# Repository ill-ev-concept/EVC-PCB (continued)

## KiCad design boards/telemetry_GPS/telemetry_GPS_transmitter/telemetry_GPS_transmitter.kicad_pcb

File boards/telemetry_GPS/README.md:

## Cart Orders

Mouser Cart(enough for 1 board, with some +/- tolerance in the number of parts): [https://www.mouser.com/en/Tools/SavedCart/Share?AccessID=581db3815b](https://www.mouser.com/en/Tools/SavedCart/Share?AccessID=141096782c)

Digikey Cart(enough for 2 transmitters, 2 receivers): [https://www.digikey.com/short/j81pmn1m](https://www.digikey.com/short/2zj99zv8)](https://www.digikey.com/short/7t22bw8j)](https://www.digikey.com/short/md8pf59v)

E-Shop Order (these need to be added to the carts):

## Block Diagram

## Common Issues/Tips

- The recommended way to solder this board is to use a stencil for the top side, place all components (except for buttons & connectors) on the solder paste, and use a reflow oven. For the back side, it's recommended to use the backside stencil as well as a heat gun. Try to be careful with applying heat around the UBLOX NEO-M8N area. DO NOT UNDER ANY CIRCUMSTANCES SOLDER THE BACK SIDE IN AN OVEN AFTER REFLOWING THE TOP SIDE.
- Always use a microscope when debugging your soldering of the telemetry "Scout" board
- Stencil
  - Make sure that the stencil is relatively flat onto the board, otherwise you'll do multiple tries and end up with way too much paste
  - Pins shouldn't have a ton of solder but always make sure to check that EVERY pin has solder
- MCU Orientation
  - The dot on the bottom left of the MCU marks pin 1, don't be fooled by anything else. If you did it correctly, the ST logo should be on the bottom left while looking at the board top-down, and the U1 label on the left side of the MCU
- BGA
  - The BALFHB uses BGA pins. These pins already come pre-tinned so do not apply solder on those pads, simply place the component down onto the pads.
  - If you suspect that the component is not flush/a couple pins are unconnected, apply flux and use the heat gun, flux is your best friend

## Instructions for a future V2 board
- Look into storing the data onto an SD card
- Add an LED to the GPS chip's PPS to verify that it is on
- Add more test points in general
- Do research into expanding the BALFHB into actual inductors and capacitors to make soldering the board less annoying

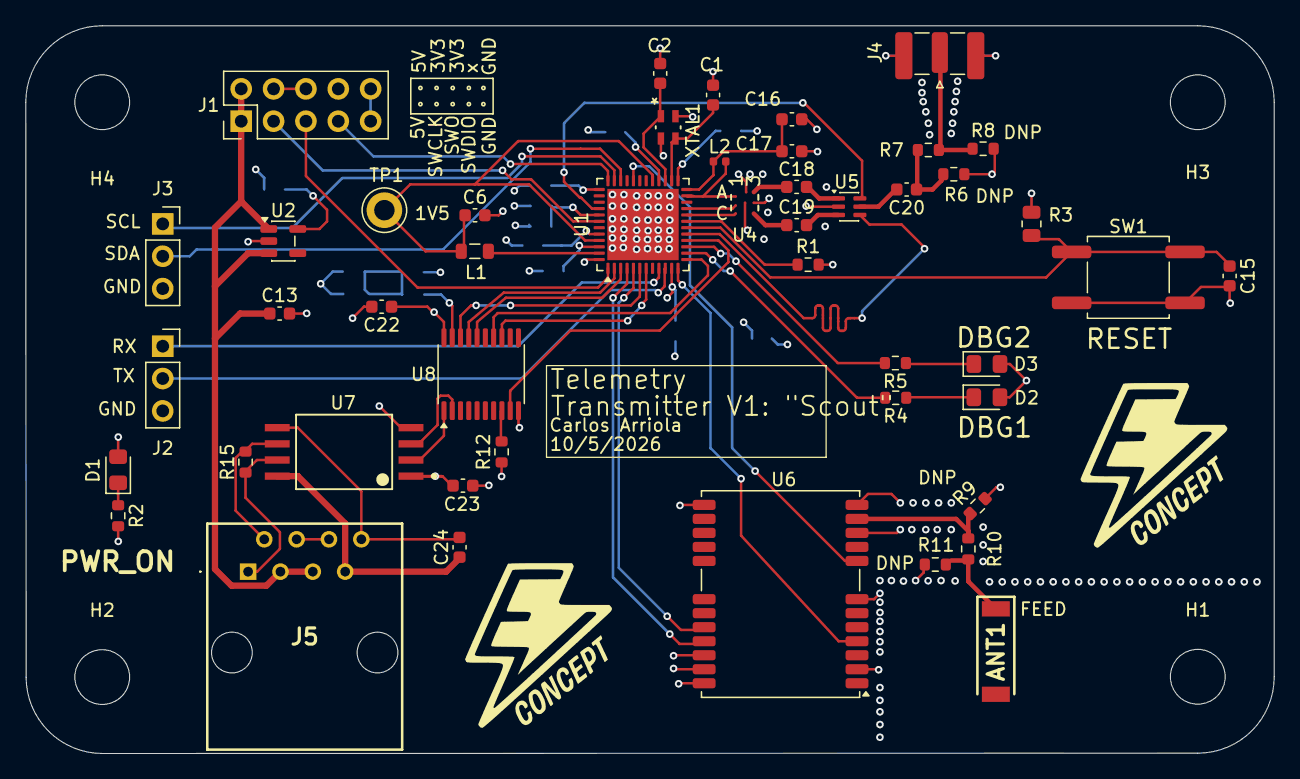
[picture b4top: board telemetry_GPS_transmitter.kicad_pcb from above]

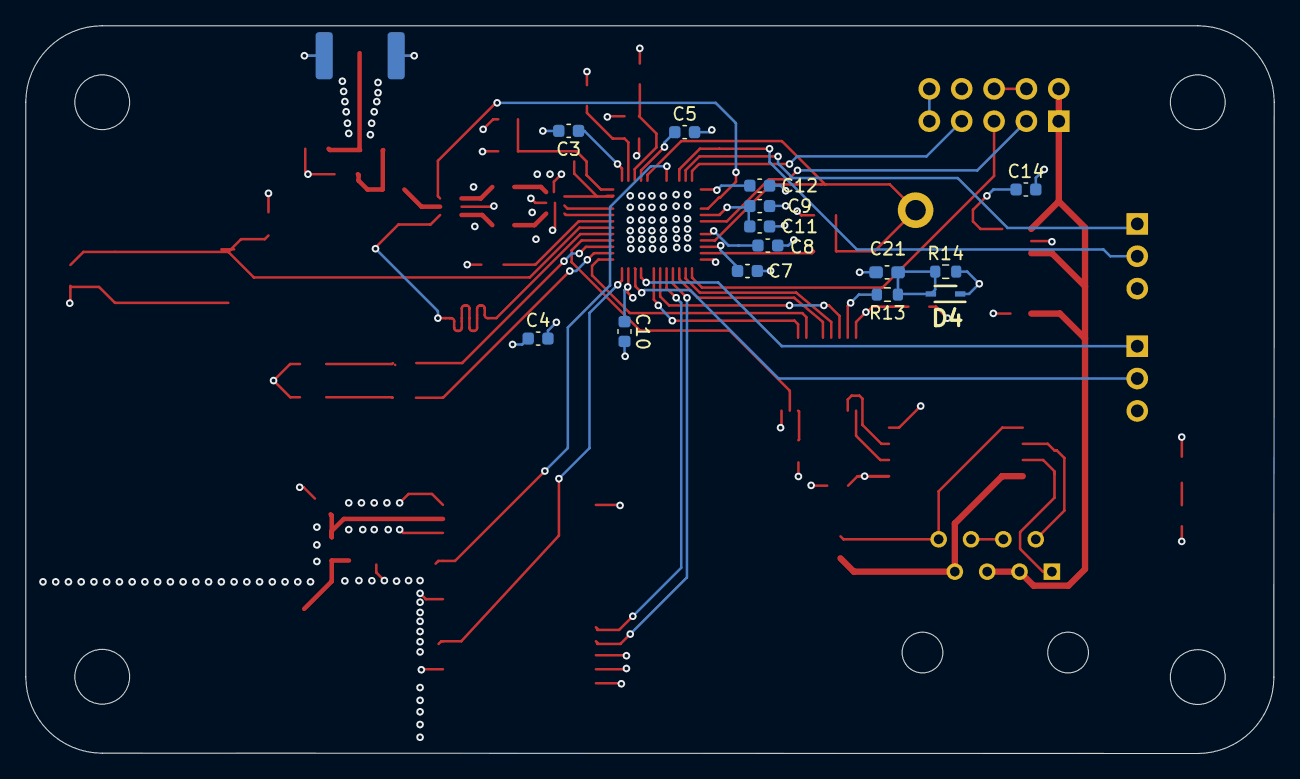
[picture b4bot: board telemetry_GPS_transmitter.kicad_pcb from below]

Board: 4 copper layers, 98.0 x 57.1 mm, 67 parts (14 on the bottom side), 55 nets.

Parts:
ANT1: 1575AT43A0040001E; ANTC7020X90N
C1, C2: 6pF; C_0603_1608Metric
C3, C5, C7, C8, C10, C15, C22, C23, C24: 0.1uF; C_0603_1608Metric
C4, C11, C12: 4.7uF; C_0603_1608Metric
C6: 470nF; C_0603_1608Metric
C9: 0.01uF; C_0603_1608Metric
C13, C14: 1uF; C_0603_1608Metric
C16: 47nF; C_0603_1608Metric
C17: 68pF; C_0603_1608Metric
C18, C19, C20: 1000pF; C_0603_1608Metric
C21: 2.2nF; C_0603_1608Metric_Pad1.08x0.95mm_HandSolder
D1, D2, D3: LED_Green; LED_0805_2012Metric_Pad1.15x1.40mm_HandSolder
D4: 1N4148WS; SODFL2512X90N
G1, G1#2: LOGO; EVC_LOGO
H1, H2, H3, H4: MountingHole; MountingHole_4.3mm_M4
J1: Conn_02x05_Odd_Even; PinHeader_2x05_P2.54mm_Vertical
J2, J3: Conn_01x03; PinSocket_1x03_P2.54mm_Vertical
J4: Conn_Coaxial; SMA_Samtec_SMA-J-P-H-ST-EM1_EdgeMount
J5: 54602-908LF; 54602908LF
L1: 15uH; L_0805_2012Metric
L2: 47nH (High Q); L_0402_1005Metric
R1: 10K; R_0603_1608Metric
R2, R4, R5: 330R; R_0603_1608Metric
R3: 100k; R_0805_2012Metric
R6, R8, R9, R11: R; R_0603_1608Metric
R7, R10: 0R; R_0603_1608Metric
R12, R13: 10k; R_0603_1608Metric
R14: 1k; R_0603_1608Metric
R15: 120R; R_0603_1608Metric
SW1: SW_Push; SW_Push_1P1T_NO_CK_KSC9xxG
TP1: TestPoint; TestPoint_Keystone_5010-5014_Multipurpose
U1: STM32WL55CCUx; QFN-48-1EP_7x7mm_P0.5mm_EP5.6x5.6mm
U2: TLV75509PDBV; SOT-23-5
U4: BALFHB-WL-02D3; CSPG8_STM
U5: MASW-007221; SOT-363_SC-70-6
U6: NEO-M8N; ublox_NEO
U7: ISO1042QDWVQ1; DWV0008A-IPC_B
U8: MCP2515-xST; TSSOP-20_4.4x6.5mm_P0.65mm
XTAL1: NX2016SA-32MHZ-EXS00A-CS07977; NX2016SA_NDK

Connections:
+1V5: C6.1, L1.1, TP1.1 (1_1), U1.29 (VDDRF1V55), U1.45 (VFBSMPS)
+3V3: C3.1, C4.1, C5.1, C7.1, C8.1, C9.1, C10.1, C11.1, C12.1, C14.1, C22.1, C23.1, D1.2 (A), D2.2 (A), D3.2 (A), D4.1 (K), J1.4, J1.6, R3.1, R14.2, U1.11 (VDD), U1.25 (VDDPA), U1.28 (VDDRF), U1.37 (VBAT), U1.41 (VDDA), U1.44 (VDD), U1.46 (VDDSMPS), U2.5 (OUT), U6.2 (D_SEL), U6.22 (V_BCKP), U6.23 (VCC), U7.1 (VCC1), U8.20 (VDD)
+5V: C13.1, J1.1, J1.2, J5.3, J5.5, U2.1 (IN), U2.3 (EN)
/CAN/5VCAN: C24.1, J5.7, U7.8 (VCC2)
/CAN/CANH: J5.1, R15.1, U7.7 (CANH)
/CAN/CANL: J5.2, R15.2, U7.6 (CANL)
/CAN/CAN_RX: U7.3 (RXD), U8.2 (RXCAN)
/CAN/CAN_TX: U7.2 (TXD), U8.1 (TXCAN)
/CAN/CS_N: U1.6 (PB8), U8.18 (~CS)
/CAN/EXT_CLK: U1.16 (PA8), U8.9 (OSC1)
/CAN/GNDCAN: C24.2, J5.8, U7.5 (GND2)
/CAN/INT_N: U1.7 (PA0), U8.13 (~INT)
/CAN/SCLK: U1.13 (PA5), U8.14 (SCK)
/CAN/SLAVE_I: U1.3 (PB5), U8.16 (SI)
/CAN/SLAVE_O: U1.2 (PB4), U8.17 (SO)
/Debug/DBG_LED_1: R4.2, U1.14 (PA6)
/Debug/DBG_LED_2: R5.2, U1.15 (PA7)
/Debug/I2C_SCL: J3.1, U1.35 (PA12)
/Debug/I2C_SDA: J3.2, U1.34 (PA11)
/Debug/MCU_UART_RX: J2.2, U1.10 (PA3)
/Debug/MCU_UART_TX: J2.1, U1.9 (PA2)
/Debug/NRST: C15.1, R3.2, SW1.1, U1.18 (NRST)
/Debug/SWCLK: J1.3, U1.42 (PA14)
/Debug/SWDIO: J1.7, U1.36 (PA13)
/Debug/SWO: J1.5, U1.1 (PB3)
/GPS/RESET_N: U1.32 (PB12), U6.8 (~RESET)
/GPS/RTC_IN: U1.12 (PA4), U6.4 (EXTINT)
/GPS/RXD: U1.4 (PB6), U6.21 (RXD/SPI_MOSI)
/GPS/TXD: U1.5 (PB7), U6.20 (TXD/SPI_MISO)
/RF/RFI_N: U1.21 (RFI_N), U4.A2 (RFI_N_OUT)
/RF/RFI_P: U1.20 (RFI_P), U4.A3 (RFI_P_OUT)
/RF/RFO_HP: L2.2, U1.23 (RFO_HP), U4.A1 (RFO_IN)
/RF/RF_I: C19.1, U4.C3 (RFI_IN)
/RF/RF_O: C18.2, U4.C1 (RFO_OUT)
/RF/RF_TX_EN: U1.40 (PC15), U5.6 (V1)
/RF/RF_TX_EN_N: U1.17 (PA9), U5.4 (V2)
/RF/VR_PA: C16.1, C17.1, L2.1, U1.24 (VR_PA)
/STM32/OSC_IN: C1.1, U1.26 (OSC_IN), XTAL1.1
/STM32/OSC_OUT: C2.1, U1.27 (OSC_OUT), XTAL1.3
GND: C1.2, C2.2, C3.2, C4.2, C5.2, C6.2, C7.2, C8.2, C9.2, C10.2, C11.2, C12.2, C13.2, C14.2, C15.2, C16.2, C17.2, C21.2, C22.2, C23.2, J1.9, J1.10, J2.3, J3.3, J4.2 (Ext), J5.4, J5.6, R1.2, R2.2, R6.2, R8.2, R9.2, R11.2, R12.1, SW1.2, U1.48 (VSSSMPS), U1.49 (VSS), U2.2 (GND), U4.B1 (GND2), U4.B2 (GND3), U4.C2 (GND1), U5.2 (GND), U6.7 (VDD_USB), U6.10 (GND), U6.12 (GND), U6.13 (GND), U6.24 (GND), U7.4 (GND1), U8.10 (VSS), XTAL1.2, XTAL1.4
unnamed: ANT1.1 (FEED_1), R10.2, R11.1
unnamed: C20.1, R6.1, R7.1
unnamed: D1.1 (K), R2.1
unnamed: D2.1 (K), R4.1
unnamed: D3.1 (K), R5.1
unnamed: C21.1, D4.2 (A), R13.1, R14.1
unnamed: J4.1 (In), R7.2, R8.1
unnamed: R1.1, U1.19 (PH3)
unnamed: L1.2, U1.47 (VLXSMPS)
unnamed: C18.1, U5.1 (RF1)
unnamed: C19.2, U5.3 (RF2)
unnamed: C20.2, U5.5 (RFC)
unnamed: R9.1, R10.1, U6.11 (RF_IN)
unnamed: R12.2, U8.8 (OSC2)
unnamed: R13.2, U8.19 (~RESET)

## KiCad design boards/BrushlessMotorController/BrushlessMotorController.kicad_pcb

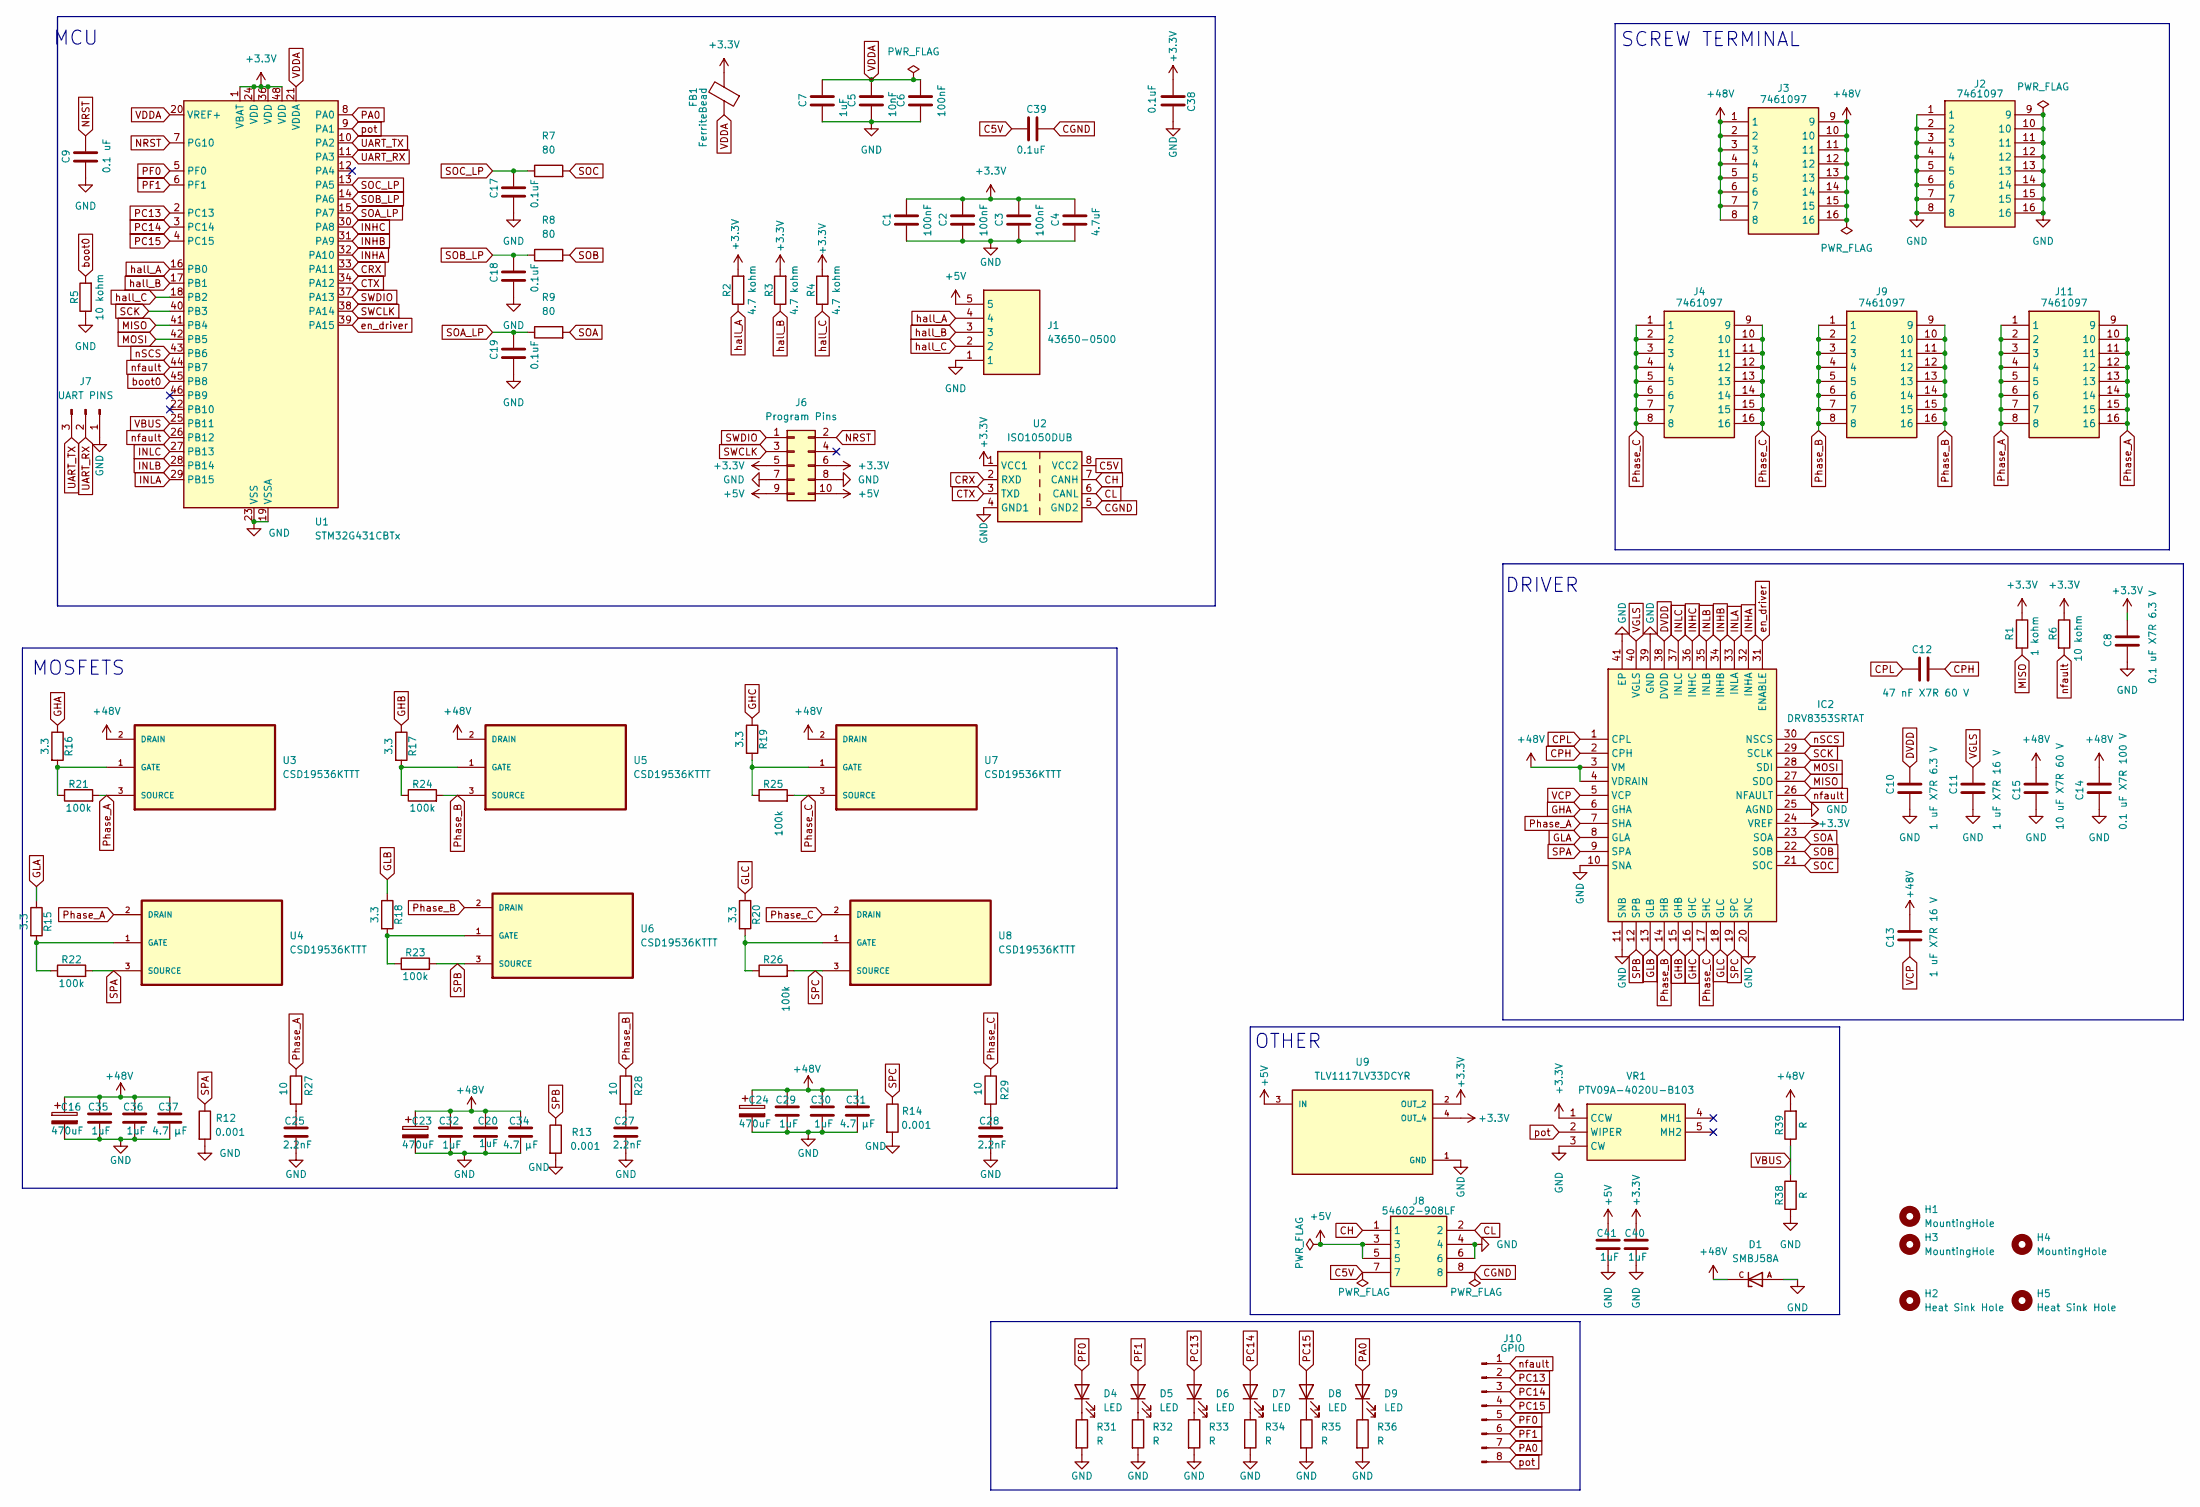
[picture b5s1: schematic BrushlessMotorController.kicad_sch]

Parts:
C1, C2, C3, C6: 100nF; C_0805_2012Metric_Pad1.18x1.45mm_HandSolder
C4: 4.7uF; C_0805_2012Metric_Pad1.18x1.45mm_HandSolder
C5: 10nF; C_0805_2012Metric_Pad1.18x1.45mm_HandSolder
C7, C40, C41: 1uF; C_0805_2012Metric_Pad1.18x1.45mm_HandSolder
C8: 0.1 uF X7R 6.3 V; C_0805_2012Metric_Pad1.18x1.45mm_HandSolder
C9: 0.1 uF; C_0805_2012Metric_Pad1.18x1.45mm_HandSolder
C10: 1 uF X7R 6.3 V; C_0805_2012Metric_Pad1.18x1.45mm_HandSolder
C11, C13: 1 uF X7R 16 V; C_0805_2012Metric_Pad1.18x1.45mm_HandSolder
C12: 47 nF X7R 60 V; C_0805_2012Metric_Pad1.18x1.45mm_HandSolder
C14: 0.1 uF X7R 100 V; C_0805_2012Metric_Pad1.18x1.45mm_HandSolder
C15: 10 uF X7R 60 V; C_1210_3225Metric_Pad1.33x2.70mm_HandSolder
C16, C23, C24: 470uF; CP_Radial_D16.0mm_P7.50mm
C17, C18, C19: 0.1uF; C_0603_1608Metric_Pad1.08x0.95mm_HandSolder
C20, C29, C30, C32, C35, C36: 1uF; C_1210_3225Metric
C25, C27, C28: 2.2nF; C_1210_3225Metric
C31, C34, C37: 4.7 µF; C_1210_3225Metric
C38, C39: 0.1uF; C_0805_2012Metric_Pad1.18x1.45mm_HandSolder
D1: SMBJ58A; DIOM4336X265N; PARTREV F2102
D4, D5, D6, D7, D8, D9: LED; LED_0603_1608Metric_Pad1.05x0.95mm_HandSolder
FB1: FerriteBead; R_0805_2012Metric_Pad1.20x1.40mm_HandSolder
H1, H3, H4: MountingHole; MountingHole_3.2mm_M3
H2, H5: Heat Sink Hole; MountingHole_3.2mm_M3
IC2: DRV8353SRTAT; QFN50P600X600X80-41N; Mouser Part Number 595-DRV8353SRTAT
J1: 43650-0500; 43650-05_00,01,02_; Mouser Part Number 538-43650-0500
J2, J3, J4, J9, J11: 7461097; Mouser Part Number 710-7461097
J6: Program Pins; PinHeader_2x05_P2.54mm_Vertical
J7: UART PINS; PinHeader_1x03_P2.54mm_Vertical
J8: 54602-908LF; 54602908LF; Manufacturer_Part_Number 54602-908LF
J10: GPIO; PinHeader_1x08_P2.54mm_Vertical
R1: 1 kohm; R_0805_2012Metric_Pad1.20x1.40mm_HandSolder
R2, R3, R4: 4.7 kohm; R_0805_2012Metric_Pad1.20x1.40mm_HandSolder
R5, R6: 10 kohm; R_0805_2012Metric_Pad1.20x1.40mm_HandSolder
R7, R8, R9: 80; R_0603_1608Metric
R12, R13, R14: 0.001; R_2512_6332Metric_Pad1.40x3.35mm_HandSolder
R15, R16, R17, R18, R19, R20: 3.3; R_0805_2012Metric_Pad1.20x1.40mm_HandSolder
R21, R22, R23, R24, R25, R26: 100k; R_0805_2012Metric_Pad1.20x1.40mm_HandSolder
R27, R28, R29: 10; R_0805_2012Metric_Pad1.20x1.40mm_HandSolder
R31, R32, R33, R34, R35, R36, R38, R39: R; R_0805_2012Metric_Pad1.20x1.40mm_HandSolder
U1: STM32G431CBTx; LQFP-48_7x7mm_P0.5mm
U2: ISO1050DUB; SOP-8_6.62x9.15mm_P2.54mm
U3, U4, U5, U6, U7, U8: CSD19536KTTT; TO254P1524X483-4N
U9: TLV1117LV33DCYR; VREG_TLV1117LV33DCYR; PARTREV B
VR1: PTV09A-4020U-B103; PTV09A4020UB103; Mouser Part Number 652-PTV09A-4020UB103

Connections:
+3.3V: C1.1, C2.1, C3.1, C4.1, C8.1, C38.2, C40.2, FB1.2, IC2.24 (VREF), J6.5, J6.6, R1.1, R2.2, R3.2, R4.2, R6.1, U1.1 (VBAT), U1.24 (VDD), U1.36 (VDD), U1.48 (VDD), U2.1 (VCC1), U9.2 (OUT_2), U9.4 (OUT_4), VR1.1 (CCW)
+5V: C41.2, J1.5, J6.9, J6.10, J8.3, J8.5, U9.3 (IN)
+48V: C13.1, C14.1, C15.1, C16.1, C20.1, C23.1, C24.1, C29.2, C30.2, C31.2, C32.2, C34.2, C35.2, C36.2, C37.2, D1.C, IC2.3 (VM), IC2.4 (VDRAIN), J3.1, J3.2, J3.3, J3.4, J3.5, J3.6, J3.7, J3.8, J3.9, J3.10, J3.11, J3.12, J3.13, J3.14, J3.15, J3.16, R39.2, U3.2 (DRAIN), U5.2 (DRAIN), U7.2 (DRAIN)
C5V: C39.2, J8.7, U2.8 (VCC2)
CGND: C39.1, J8.8, U2.5 (GND2)
CH: J8.1, U2.7 (CANH)
CL: J8.2, U2.6 (CANL)
CPH: C12.1, IC2.2 (CPH)
CPL: C12.2, IC2.1 (CPL)
CRX: U1.33 (PA11), U2.2 (RXD)
CTX: U1.34 (PA12), U2.3 (TXD)
DVDD: C10.1, IC2.38 (DVDD)
GHA: IC2.6 (GHA), R16.1
GHB: IC2.15 (GHB), R17.1
GHC: IC2.16 (GHC), R19.1
GLA: IC2.8 (GLA), R15.1
GLB: IC2.13 (GLB), R18.1
GLC: IC2.18 (GLC), R20.1
GND: C1.2, C2.2, C3.2, C4.2, C5.2, C6.2, C7.2, C8.2, C9.2, C10.2, C11.2, C14.2, C15.2, C16.2, C17.2, C18.2, C19.2, C20.2, C23.2, C24.2, C25.1, C27.1, C28.1, C29.1, C30.1, C31.1, C32.1, C34.1, C35.1, C36.1, C37.1, C38.1, C40.1, C41.1, D1.A, IC2.10 (SNA), IC2.11 (SNB), IC2.20 (SNC), IC2.25 (AGND), IC2.39 (GND), IC2.41 (EP), J1.1, J2.1, J2.2, J2.3, J2.4, J2.5, J2.6, J2.7, J2.8, J2.9, J2.10, J2.11, J2.12, J2.13, J2.14, J2.15, J2.16, J6.7, J6.8, J7.1, J8.4, J8.6, R5.1, R12.2, R13.2, R14.2, R31.2, R32.2, R33.2, R34.2, R35.2, R36.2, R38.1, U1.19 (VSSA), U1.23 (VSS), U1.35 (VSS), U1.47 (VSS), U2.4 (GND1), U9.1 (GND), VR1.3 (CW)
INHA: IC2.32 (INHA), U1.32 (PA10)
INHB: IC2.34 (INHB), U1.31 (PA9)
INHC: IC2.36 (INHC), U1.30 (PA8)
INLA: IC2.33 (INLA), U1.29 (PB15)
INLB: IC2.35 (INLB), U1.28 (PB14)
INLC: IC2.37 (INLC), U1.27 (PB13)
MISO: IC2.27 (SDO), R1.2, U1.41 (PB4)
MOSI: IC2.28 (SDI), U1.42 (PB5)
NRST: C9.1, J6.2, U1.7 (PG10)
unnamed: C25.2, R27.2
unnamed: C27.2, R28.2
unnamed: C28.2, R29.2
unnamed: D4.1 (K), R31.1
unnamed: D5.1 (K), R32.1
unnamed: D6.1 (K), R33.1
unnamed: D7.1 (K), R34.1
unnamed: D8.1 (K), R35.1
unnamed: D9.1 (K), R36.1
unnamed: R16.2, R21.1, U3.1 (GATE)
unnamed: R15.2, R22.1, U4.1 (GATE)
unnamed: R17.2, R24.1, U5.1 (GATE)
unnamed: R18.2, R23.1, U6.1 (GATE)
unnamed: R19.2, R25.1, U7.1 (GATE)
unnamed: R20.2, R26.1, U8.1 (GATE)
PA0: D9.2 (A), J10.7, U1.8 (PA0)
PC13: D6.2 (A), J10.2, U1.2 (PC13)
PC14: D7.2 (A), J10.3, U1.3 (PC14)
PC15: D8.2 (A), J10.4, U1.4 (PC15)
PF0: D4.2 (A), J10.5, U1.5 (PF0)
PF1: D5.2 (A), J10.6, U1.6 (PF1)
Phase_A: IC2.7 (SHA), J11.1, J11.2, J11.3, J11.4, J11.5, J11.6, J11.7, J11.8, J11.9, J11.10, J11.11, J11.12, J11.13, J11.14, J11.15, J11.16, R21.2, R27.1, U3.3 (SOURCE), U4.2 (DRAIN)
Phase_B: IC2.14 (SHB), J9.1, J9.2, J9.3, J9.4, J9.5, J9.6, J9.7, J9.8, J9.9, J9.10, J9.11, J9.12, J9.13, J9.14, J9.15, J9.16, R24.2, R28.1, U5.3 (SOURCE), U6.2 (DRAIN)
Phase_C: IC2.17 (SHC), J4.1, J4.2, J4.3, J4.4, J4.5, J4.6, J4.7, J4.8, J4.9, J4.10, J4.11, J4.12, J4.13, J4.14, J4.15, J4.16, R25.2, R29.1, U7.3 (SOURCE), U8.2 (DRAIN)
SCK: IC2.29 (SCLK), U1.40 (PB3)
SOA: IC2.23 (SOA), R9.2
SOA_LP: C19.1, R9.1, U1.15 (PA7)
SOB: IC2.22 (SOB), R8.2
SOB_LP: C18.1, R8.1, U1.14 (PA6)
SOC: IC2.21 (SOC), R7.2
SOC_LP: C17.1, R7.1, U1.13 (PA5)
SPA: IC2.9 (SPA), R12.1, R22.2, U4.3 (SOURCE)
SPB: IC2.12 (SPB), R13.1, R23.2, U6.3 (SOURCE)
SPC: IC2.19 (SPC), R14.1, R26.2, U8.3 (SOURCE)
SWCLK: J6.3, U1.38 (PA14)
SWDIO: J6.1, U1.37 (PA13)
UART_RX: J7.2, U1.11 (PA3)
UART_TX: J7.3, U1.10 (PA2)
VBUS: R38.2, R39.1, U1.25 (PB11)
VCP: C13.2, IC2.5 (VCP)
VDDA: C5.1, C6.1, C7.1, FB1.1, U1.20 (VREF+), U1.21 (VDDA)
VGLS: C11.1, IC2.40 (VGLS)
boot0: R5.2, U1.45 (PB8)
en_driver: IC2.31 (ENABLE), U1.39 (PA15)
hall_A: J1.4, R2.1, U1.16 (PB0)
hall_B: J1.3, R3.1, U1.17 (PB1)
hall_C: J1.2, R4.1, U1.18 (PB2)
nSCS: IC2.30 (NSCS), U1.43 (PB6)
nfault: IC2.26 (NFAULT), J10.1, R6.2, U1.26 (PB12), U1.44 (PB7)
pot: J10.8, U1.9 (PA1), VR1.2 (WIPER)

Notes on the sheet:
OTHER
SCREW TERMINAL
MOSFETS
MCU
DRIVER

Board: 2 copper layers, 106 parts (0 on the bottom side), 78 nets, no tracks yet.

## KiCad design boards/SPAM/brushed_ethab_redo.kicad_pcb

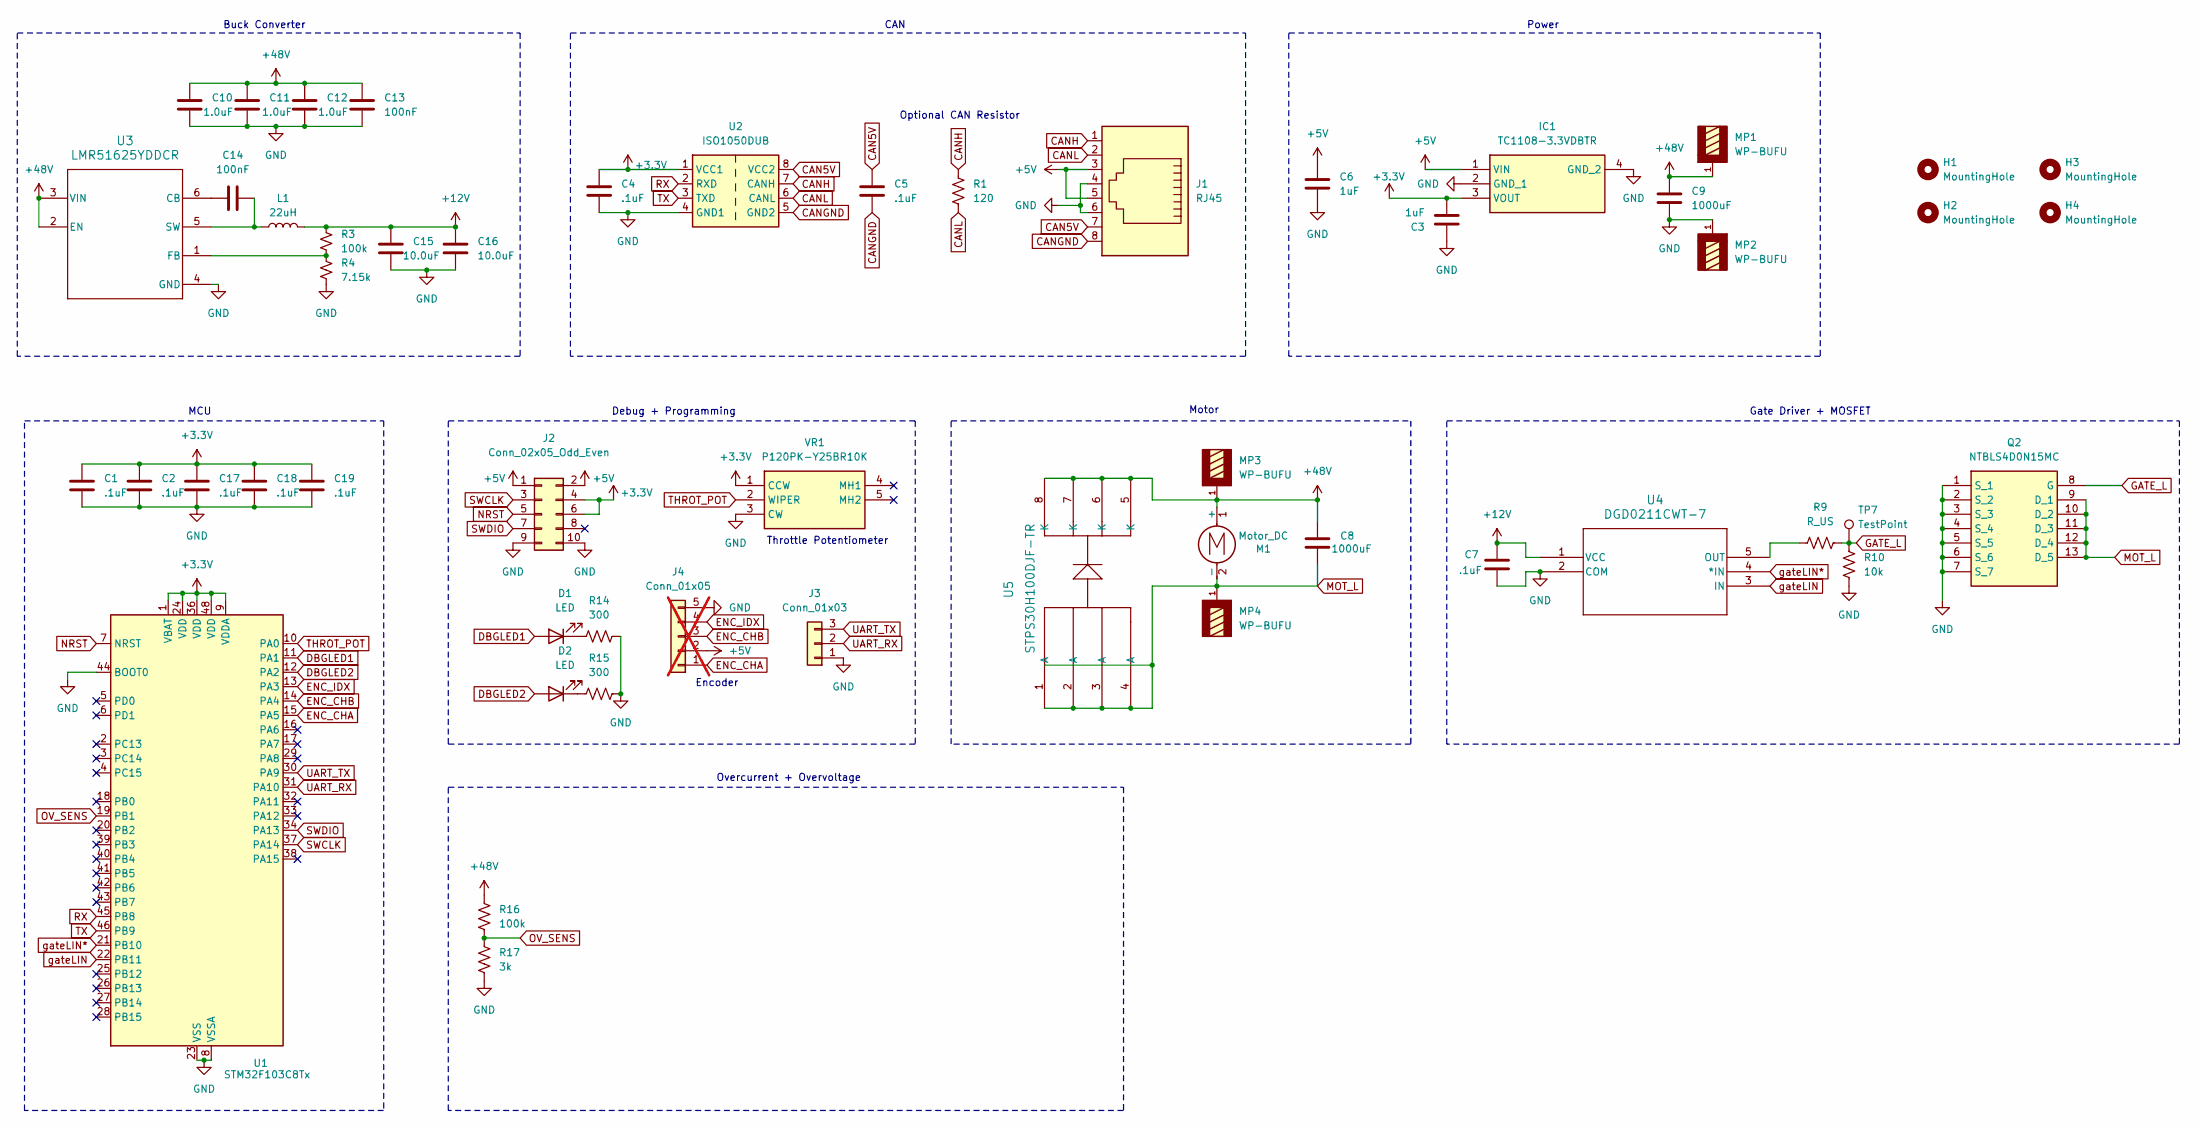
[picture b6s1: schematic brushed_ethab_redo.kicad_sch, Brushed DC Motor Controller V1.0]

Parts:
C1, C2, C4, C5, C7, C17, C18, C19: .1uF; C_0805_2012Metric_Pad1.18x1.45mm_HandSolder
C3, C6: 1uF; C_0805_2012Metric_Pad1.18x1.45mm_HandSolder
C8, C9: 1000uF; CP_Radial_D18.0mm_P7.50mm
C10, C11, C12: 1.0uF; C_1206_3216Metric
C13: 100nF; C_0603_1608Metric_Pad1.08x0.95mm_HandSolder
C14: 100nF; C_0402_1005Metric_Pad0.74x0.62mm_HandSolder
C15, C16: 10.0uF; C_1210_3225Metric
D1, D2: LED; LED_0805_2012Metric_Pad1.15x1.40mm_HandSolder
H1, H2, H3, H4: MountingHole; MountingHole_4.3mm_M4
IC1: TC1108-3.3VDBTR; SOT230P700X180-4N; Manufacturer_Part_Number TC1108-3.3VDBTR; Mouser Part Number 579-TC1108-3.3VDBTR
J1: RJ45; RJ45_Amphenol_54602-x08_Horizontal
J2: Conn_02x05_Odd_Even; PinSocket_2x05_P2.54mm_Vertical
J3: Conn_01x03; PinSocket_1x03_P2.54mm_Vertical
J4: Conn_01x05; PinSocket_1x05_P2.54mm_Vertical; not fitted
L1: 22uH; L_Bourns_SRR1208_12.7x12.7mm
M1: Motor_DC
MP1, MP2, MP3, MP4: WP-BUFU; WP-BUFU_7461097; DigiKey_Part_Number 732-3217-ND
Q2: NTBLS4D0N15MC; Manufacturer_Part_Number NTBLS4D0N15MC; Mouser Part Number 863-NTBLS4D0N15MC
R1: 120; R_0805_2012Metric_Pad1.20x1.40mm_HandSolder
R3: 100k; R_0402_1005Metric_Pad0.72x0.64mm_HandSolder
R4: 7.15k; R_0603_1608Metric_Pad0.98x0.95mm_HandSolder
R9: R_US; R_0805_2012Metric_Pad1.20x1.40mm_HandSolder
R10: 10k; R_0805_2012Metric_Pad1.20x1.40mm_HandSolder
R14, R15: 300; R_0805_2012Metric_Pad1.20x1.40mm_HandSolder
R16: 100k; R_0805_2012Metric_Pad1.20x1.40mm_HandSolder
R17: 3k; R_0805_2012Metric_Pad1.20x1.40mm_HandSolder
TP7: TestPoint; TestPoint_Pad_D1.0mm
U1: STM32F103C8Tx; LQFP-48_7x7mm_P0.5mm
U2: ISO1050DUB; SOP-8_6.62x9.15mm_P2.54mm
U3: LMR51625YDDCR; DDC0006A-MFG
U4: DGD0211CWT-7; TSOT25-TH_DIO
U5: STPS30H100DJF-TR; MOSFET_100DJF-TR_STM
VR1: P120PK-Y25BR10K; P120PKY25BR10K; Manufacturer_Part_Number P120PK-Y25BR10K; Mouser Part Number 858-P120PKY25BR10K

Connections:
+3.3V: C1.1, C2.1, C3.2, C4.1, C17.1, C18.1, C19.1, IC1.3 (VOUT), J2.4, J2.6, U1.1 (VBAT), U1.9 (VDDA), U1.24 (VDD), U1.36 (VDD), U1.48 (VDD), U2.1 (VCC1), VR1.1 (CCW)
+5V: C6.1, IC1.1 (VIN), J1.3, J1.5, J2.1, J2.2, J4.2
+12V: C7.1, C15.1, C16.1, L1.2, R3.1, U4.1 (VCC)
+48V: C8.1, C9.1, C10.1, C11.1, C12.1, C13.1, M1.1 (+), MP1.1, MP1.2, MP1.3, MP1.4, MP1.5, MP1.6, MP1.7, MP1.8, MP1.9, MP1.10, MP1.11, MP1.12, MP1.13, MP1.14, MP1.15, MP1.16, MP3.1, MP3.2, MP3.3, MP3.4, MP3.5, MP3.6, MP3.7, MP3.8, MP3.9, MP3.10, MP3.11, MP3.12, MP3.13, MP3.14, MP3.15, MP3.16, R16.2, U3.2 (EN), U3.3 (VIN), U5.5 (K), U5.6 (K), U5.7 (K), U5.8 (K)
CAN5V: C5.1, J1.7, U2.8 (VCC2)
CANGND: C5.2, J1.8, U2.5 (GND2)
CANH: J1.1, R1.1, U2.7 (CANH)
CANL: J1.2, R1.2, U2.6 (CANL)
DBGLED1: D1.2 (A), U1.11 (PA1)
DBGLED2: D2.2 (A), U1.12 (PA2)
ENC_CHA: J4.1, U1.15 (PA5)
ENC_CHB: J4.3, U1.14 (PA4)
ENC_IDX: J4.4, U1.13 (PA3)
GATE_L: Q2.8 (G), R9.2, R10.2, TP7.1 (1_1)
GND: C1.2, C2.2, C3.1, C4.2, C6.2, C7.2, C9.2, C10.2, C11.2, C12.2, C13.2, C15.2, C16.2, C17.2, C18.2, C19.2, IC1.2 (GND_1), IC1.4 (GND_2), J1.4, J1.6, J2.9, J2.10, J3.1, J4.5, MP2.1, MP2.2, MP2.3, MP2.4, MP2.5, MP2.6, MP2.7, MP2.8, MP2.9, MP2.10, MP2.11, MP2.12, MP2.13, MP2.14, MP2.15, MP2.16, Q2.1 (S_1), Q2.2 (S_2), Q2.3 (S_3), Q2.4 (S_4), Q2.5 (S_5), Q2.6 (S_6), Q2.7 (S_7), R4.2, R10.1, R14.2, R15.2, R17.1, U1.8 (VSSA), U1.23 (VSS), U1.35 (VSS), U1.44 (BOOT0), U1.47 (VSS), U2.4 (GND1), U3.4 (GND), U4.2 (COM), VR1.3 (CW)
MOT_L: C8.2, M1.2 (-), MP4.1, MP4.2, MP4.3, MP4.4, MP4.5, MP4.6, MP4.7, MP4.8, MP4.9, MP4.10, MP4.11, MP4.12, MP4.13, MP4.14, MP4.15, MP4.16, Q2.9 (D_1), Q2.10 (D_2), Q2.11 (D_3), Q2.12 (D_4), Q2.13 (D_5), U5.1 (A), U5.2 (A), U5.3 (A), U5.4 (A)
NRST: J2.5, U1.7 (NRST)
unnamed: D1.1 (K), R14.1
unnamed: D2.1 (K), R15.1
unnamed: C14.1, U3.6 (CB)
unnamed: R3.2, R4.1, U3.1 (FB)
unnamed: C14.2, L1.1, U3.5 (SW)
unnamed: R9.1, U4.5 (OUT)
OV_SENS: R16.1, R17.2, U1.19 (PB1)
RX: U1.45 (PB8), U2.2 (RXD)
SWCLK: J2.3, U1.37 (PA14)
SWDIO: J2.7, U1.34 (PA13)
THROT_POT: U1.10 (PA0), VR1.2 (WIPER)
TX: U1.46 (PB9), U2.3 (TXD)
UART_RX: J3.2, U1.31 (PA10)
UART_TX: J3.3, U1.30 (PA9)
gateLIN: U1.22 (PB11), U4.3 (IN)
gateLIN*: U1.21 (PB10), U4.4 (*IN)

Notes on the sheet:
Buck Converter
Power
Encoder
Optional CAN Resistor
Throttle Potentiometer
Motor
MCU
CAN
Gate Driver + MOSFET
Overcurrent + Overvoltage
Debug + Programming

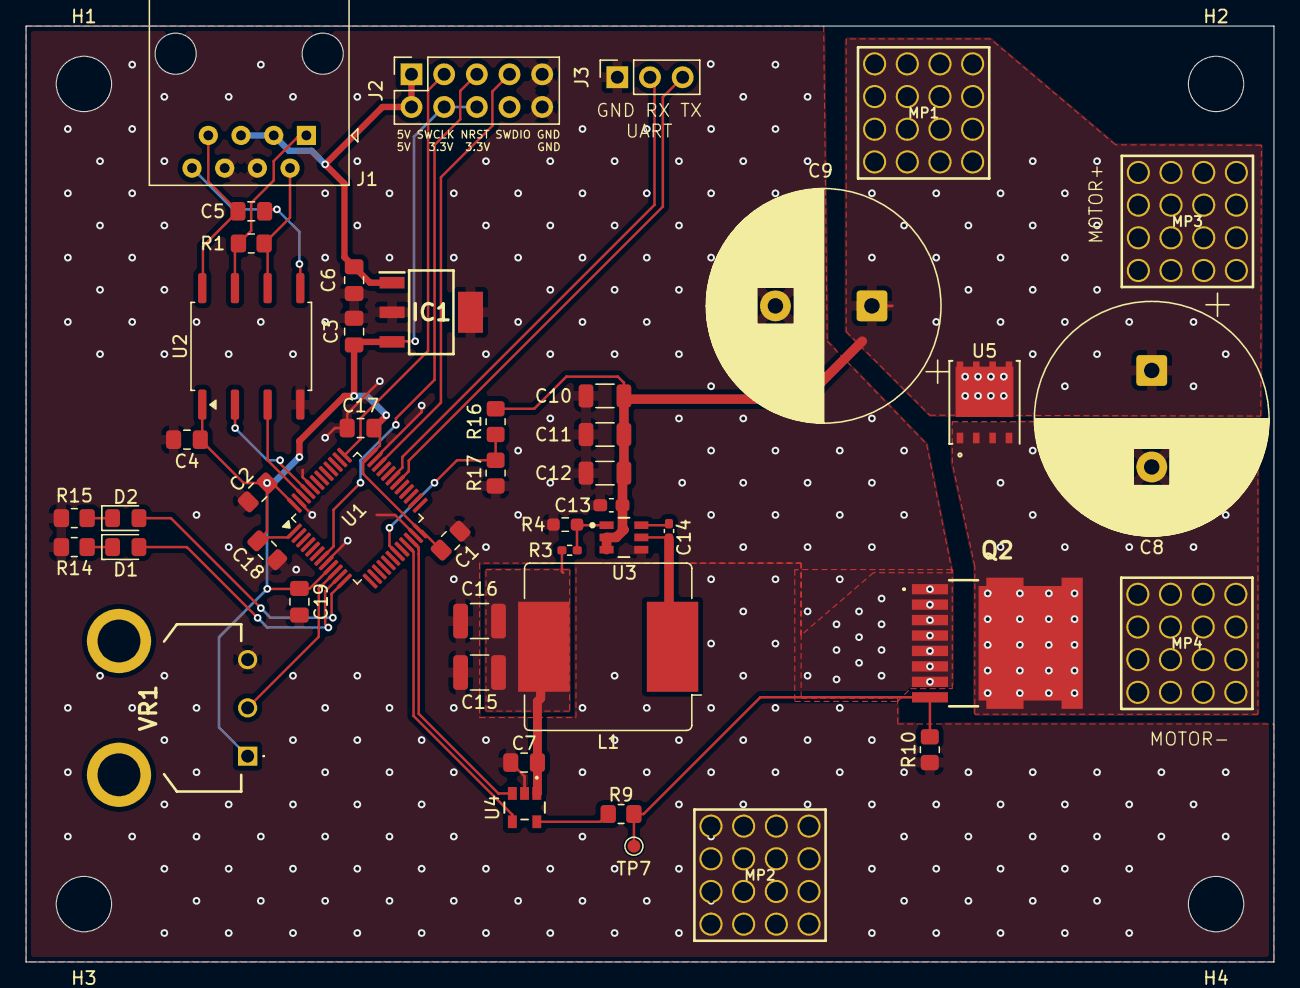
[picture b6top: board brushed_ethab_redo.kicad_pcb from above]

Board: 2 copper layers, 97.0 x 72.8 mm, 51 parts (0 on the bottom side), 30 nets.
